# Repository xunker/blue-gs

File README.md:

# BlueGS: Internal BlueSCSI for Apple IIgs and //e

*BlueGS* is the internal hard drive your Apple IIgs and //e always *craved*.

Using the [BlueSCSI](https://github.com/erichelgeson/BlueSCSI) SCSI drive emulator and your compatible SCSI card, you have a fully internal hard drive with accessible microSD slot while still keeping your DB-25 connector free for other peripherals.

# How it works

BlueGS connects between your SCSI card and its external DB-25 connector to give you a seamless installation. The BlueGS module itself mounts in a free DB-25 connector cutout in the rear of your IIgs or //e.

# Features

* Gives your Apple IIgs or //e an internal, cable-free hard drive
* Can be powered from SCSI termination power only (if present)
* "Termination Power" mod is not required (when powered from auxiliary 5V source)
* Can *provide* termination power to the SCSI bus (when powered from a 5V source such as the Game IO connector or card slot)
* Built-in termination that is controlled with a single switch
* Active termination ICs instead of passive termination resistors, reduces power consumption by over 2/3rds
* Reverse current and voltage protection with overcurrent prevention for auxiliary 5V input
* Connection for external drive activity LED

# Compatible SCSI cards

Tested:
* [GGLabs A2SCSI](https://gglabs.us/node/2071) - a clone of the Apple Rev C SCSI card
* Apple Rev C SCSI and clones
* Apple High-Speed SCSI ("Sandwich II")
* Ramfast SCSI

Assumed to work:
* GSE-Reactive SCSI Card

Untested:
* AMR SCSI
* Cirtech SCSI/Insyder
* SVA Hard Disk Adapter

The CMS SCSI II is currently confirmed **NOT** to work, though it appears to be a (card) firmware issue and not a "bug" with BlueSCSI.

## What if my SCSI card doesn't provide termination power?

Running BlueGS from "termination power" makes installation much easier, but not all SCSI cards have it. For more details, please check out the notes on [Powering BlueGS](POWERING_BLUE-GS.md).

# Performance

Using [BenchmarkD](https://www.brutaldeluxe.fr/products/apple2gs/benchmarked.html) with Apple IIgs (ROM 1, "Fast" speed), GS-RAM Plus w/ 2MB, GGLabs A2SCSI card. Using Blue-Pill-based BlueGS board.

* Read
  * File: 52 KB/s
  * Block-by-block: 36 KB/s
  * With 64K buffer: 79 KB/s
* Write (File): 37 KB/s

# Can I use it on things besides the IIgs and //e?

Yes! It's a standard BlueSCSI device and uses the standard BlueSCSI V1 firmware. In fact, the built-in DB-25 connector makes it the perfect external SCSI drive as well!

BlueGS can be mounted internally in any computer that has an open cutout for a DB-25 connector.

## ✅ Compatible Apple clones

These computers *do* have rear DB-25 cutouts and so BlueGS should be able to mount properly, but are untested.

* Franklin Ace 2000/2100/2200
* Basis 108

## 🚫 Apple II/II+ and similar clones

BlueGS will function in an Apple II or II+, but you will not be able to mount it because it uses "V" shaped cutouts instead of D-Subminiature connector cutouts like the //e and IIgs have.

Many Apple II clones use the same rear cutout design and have the same mounting limitation. **A mounting solution for these machine is planned**.

* Franklin Ace 100/1000/1200
* Pravetz-8
  - Includes the -8, -82, -8M, -8A, -8E, and -8C
* Unitron (Brazil)
* Ci Base-48 and Pineapple (Korea)

# Assembly

If you purchased BlueGS as a self-assemble kit or are using your own PCBs, please follow the instructions in the "[assembly](assembly/)" directory.

If your BlueGS was purchased fully-assembled, please move on to the "[Installation](installation/)" section.
# Installation

Installation guides can be found in the "[installation](installation/)" directory.
# Schematics

[V1.4 Schematic](schematics/schematic_v1.4.pdf) (**FINAL**, recommended design)

<details>
  <summary>Older Schematics</summary>

[V1.3 Schematic](schematics/schematic_v1.3.pdf)

[V1.2 Schematic](schematics/schematic_v1.2.pdf)

[V1.1 Schematic](schematics/schematic_v1.1.pdf)

</details>

# EDA/Kicad and Gerber Files

Kicad of current design can be found in [kicad](kicad/) directory.

# Credits

This project would not be possible without the work done by [ztto](https://github.com/ztto/ArdSCSino-stm32), [Tambo](https://twitter.com/h_koma2), [Eric Helgeson](https://github.com/erichelgeson/BlueSCSI), [Androda](https://androda.work/), and many others.

The "Blue Pill" footprint was originally created by [Yet-Another-Average-Joe](https://github.com/yet-another-average-joe/Kicad-STM32).

Symbol and footprint for Molex 105162-0001 MicroSD slot created by [SnapEDA user HMantz](https://www.snapeda.com/parts/105162-0001/Molex/view-part/).

# License

See [LICENSE.md](LICENSE.md).

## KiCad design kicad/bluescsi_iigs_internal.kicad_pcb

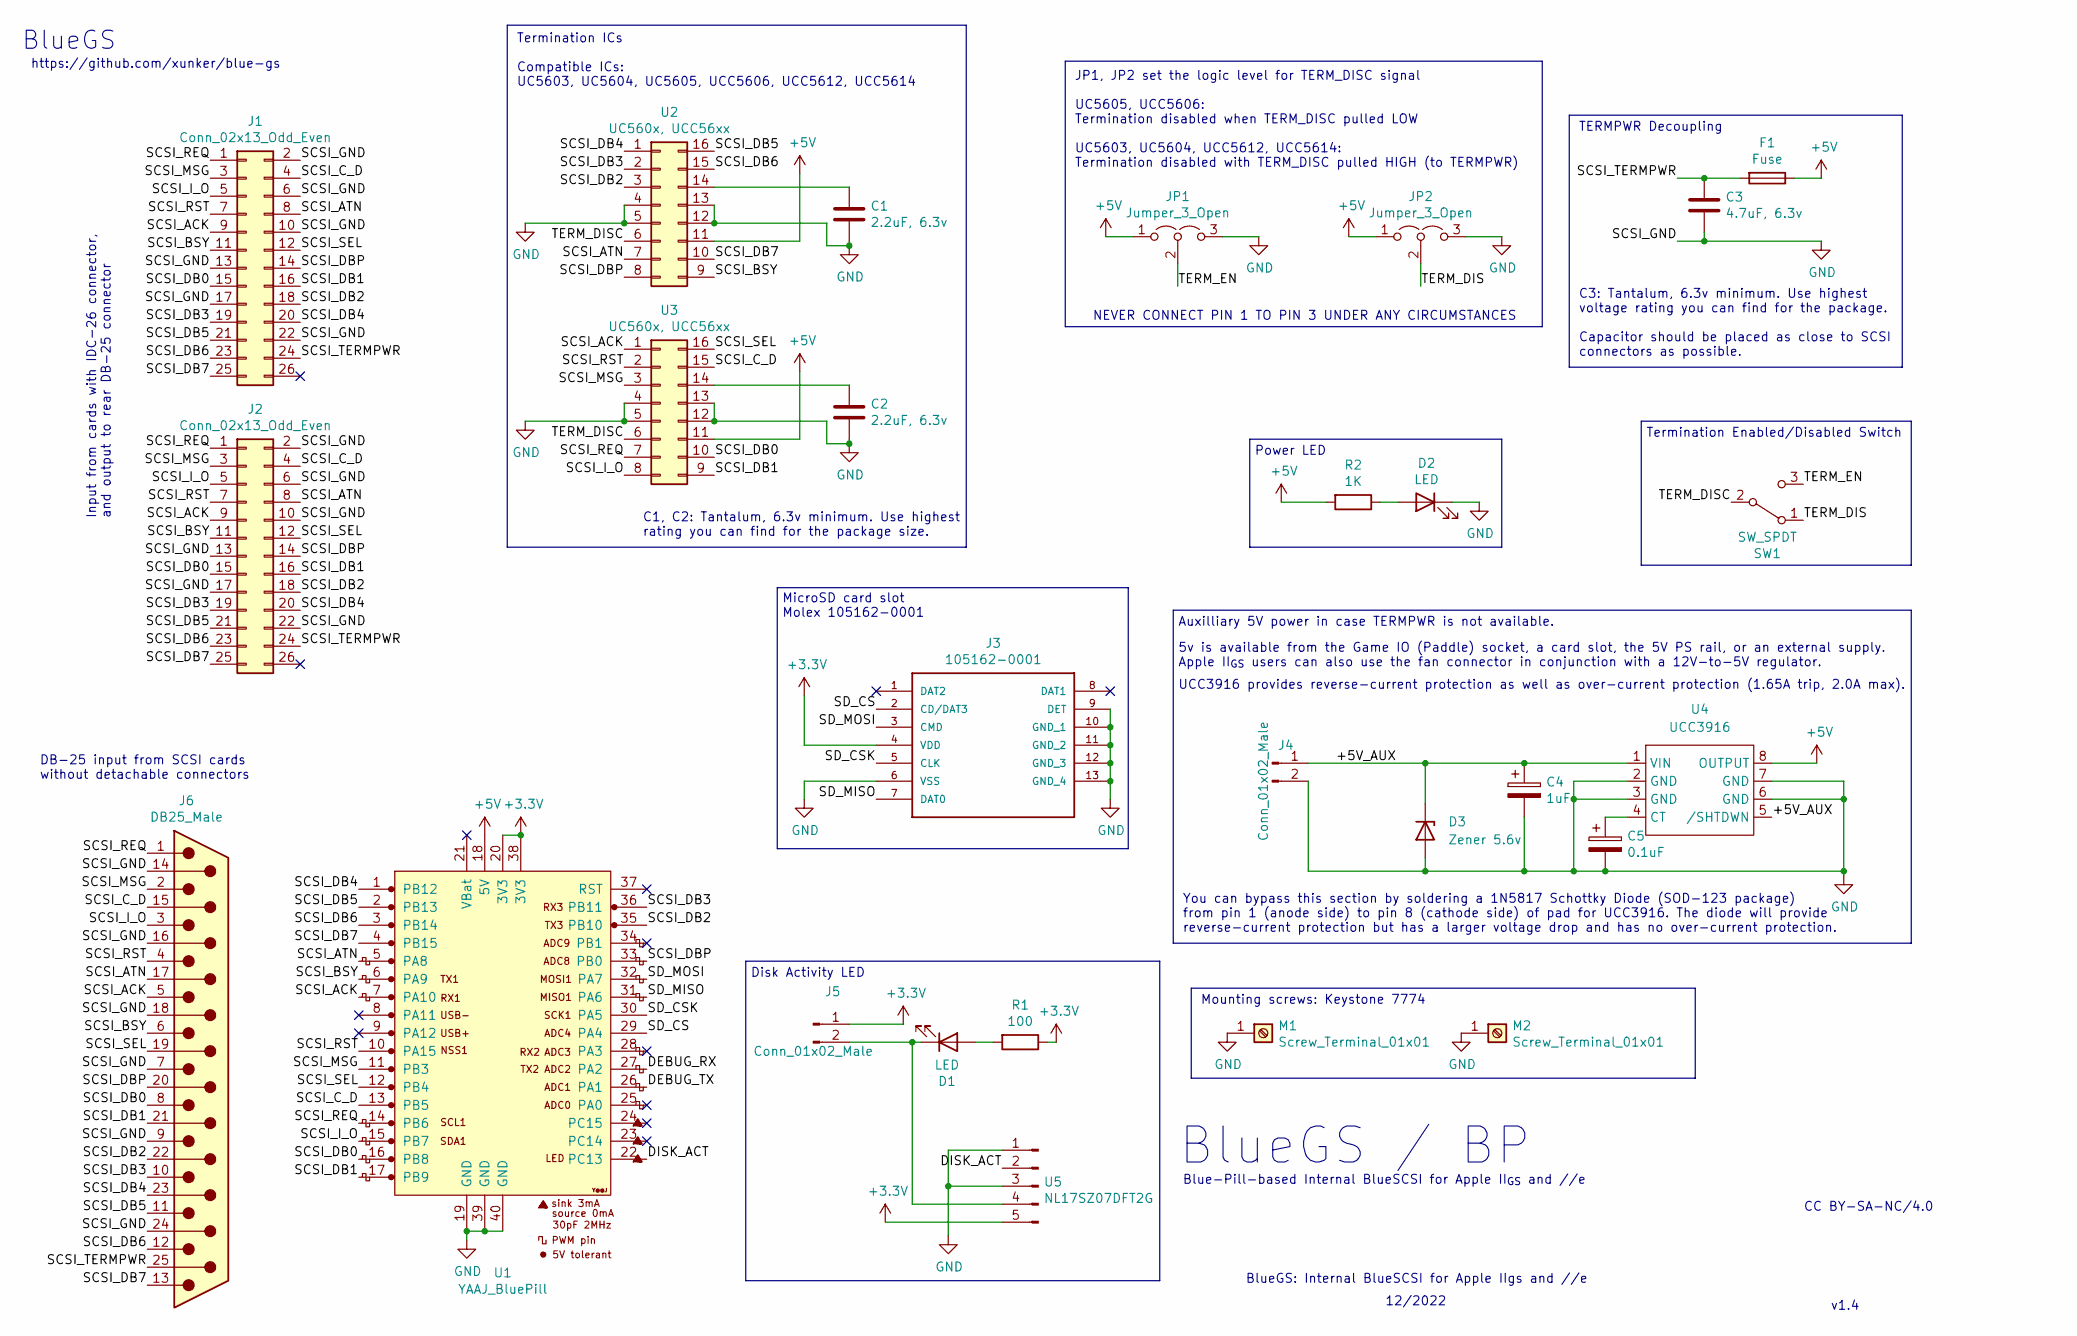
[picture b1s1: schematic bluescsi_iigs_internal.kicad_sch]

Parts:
C1, C2: 2.2uF, 6.3v; CP_EIA-3528-21_Kemet-B_Pad1.50x2.35mm_HandSolder; MANUFACTURER_PART_NUMBER TAJB225M020RNJ; LCSC part number C444753
C3: 4.7uF, 6.3v; CP_EIA-3528-21_Kemet-B_Pad1.50x2.35mm_HandSolder; MANUFACTURER_PART_NUMBER T494B475K016AT; LCSC part number C918865
C4: 1uF; CP_EIA-3528-21_Kemet-B_Pad1.50x2.35mm_HandSolder; MANUFACTURER_PART_NUMBER T491B105K025AT; LCSC part number C452761
C5: 0.1uF; CP_EIA-3216-10_Kemet-I; MANUFACTURER_PART_NUMBER T491A104K035AT; LCSC part number C122257
D1: LED; LED_0805_2012Metric_Pad1.15x1.40mm_HandSolder; MANUFACTURER_PART_NUMBER HL-PSC-2012H203BC; LCSC part number C497961
D2: LED; LED_0805_2012Metric_Pad1.15x1.40mm_HandSolder; MANUFACTURER_PART_NUMBER NCD0805R1; LCSC part number C84256
D3: Zener 5.6v; D_SOD-123; MANUFACTURER_PART_NUMBER MMSZ5232A_R1_00001; LCSC part number C268592
F1: Fuse; Fuse_1210_3225Metric; MANUFACTURER_PART_NUMBER CFS12V6TR80; LCSC part number C163134
J1, J2: Conn_02x13_Odd_Even; PinHeader_2x13_P2.54mm_Vertical
J3: 105162-0001; MOUSER_PART_NUMBER 538-105162-0001
J4, J5: Conn_01x02_Male; PinHeader_1x02_P2.54mm_Vertical
J6: DB25_Male; DSUB-25_Male_EdgeMount_P2.77mm
JP1, JP2: Jumper_3_Open; SolderJumper-3_P1.3mm_Open_Pad1.0x1.5mm_NumberLabels
M1, M2: Screw_Terminal_01x01; keystone-7774
R1: 100; R_0805_2012Metric_Pad1.20x1.40mm_HandSolder; MANUFACTURER_PART_NUMBER 0805W8F1000T5E; LCSC part number C17408
R2: 1K; R_0805_2012Metric_Pad1.20x1.40mm_HandSolder; MANUFACTURER_PART_NUMBER 0805W8F1001T5E; LCSC part number C17513
SW1: SW_SPDT; SW_SPDT_PCM12; MANUFACTURER_PART_NUMBER PCM12SMTR; LCSC part number C221841
U1: YAAJ_BluePill; YAAJ_BluePill_2
U2, U3: UC560x, UCC56xx; SOIC127P600X175-16N
U4: UCC3916; SOIC-8_3.9x4.9mm_P1.27mm
U5: NL17SZ07DFT2G; SOT-353_SC-70-5_Handsoldering; MANUFACTURER_PART_NUMBER NL17SZ07DFT2G; LCSC part number C113255

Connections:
+3V3: J3.4 (VDD), J5.1, R1.1, U1.20 (3V3), U1.38 (3V3), U5.5
+5V: F1.1, JP1.1 (A), JP2.1 (A), R2.2, U1.18 (5V), U2.11, U3.11, U4.8 (OUTPUT)
/+5V_AUX: C4.1, D3.1 (K), J4.1, U4.1 (VIN), U4.5 (/SHTDWN)
/DEBUG_RX: U1.27 (PA2)
/DEBUG_TX: U1.26 (PA1)
/DISK_ACT: U1.22 (PC13), U5.2
/SCSI_ACK: J1.9, J2.9, J6.5, U1.7 (PA10), U3.1
/SCSI_ATN: J1.8, J2.8, J6.17, U1.5 (PA8), U2.7
/SCSI_BSY: J1.11, J2.11, J6.6, U1.6 (PA9), U2.9
/SCSI_C_D: J1.4, J2.4, J6.15, U1.13 (PB5), U3.15
/SCSI_DB0: J1.15, J2.15, J6.8, U1.16 (PB8), U3.10
/SCSI_DB1: J1.16, J2.16, J6.21, U1.17 (PB9), U3.9
/SCSI_DB2: J1.18, J2.18, J6.22, U1.35 (PB10), U2.3
/SCSI_DB3: J1.19, J2.19, J6.10, U1.36 (PB11), U2.2
/SCSI_DB4: J1.20, J2.20, J6.23, U1.1 (PB12), U2.1
/SCSI_DB5: J1.21, J2.21, J6.11, U1.2 (PB13), U2.16
/SCSI_DB6: J1.23, J2.23, J6.12, U1.3 (PB14), U2.15
/SCSI_DB7: J1.25, J2.25, J6.13, U1.4 (PB15), U2.10
/SCSI_DBP: J1.14, J2.14, J6.20, U1.33 (PB0), U2.8
/SCSI_I_O: J1.5, J2.5, J6.3, U1.15 (PB7), U3.8
/SCSI_MSG: J1.3, J2.3, J6.2, U1.11 (PB3), U3.3
/SCSI_REQ: J1.1, J2.1, J6.1, U1.14 (PB6), U3.7
/SCSI_RST: J1.7, J2.7, J6.4, U1.10 (PA15), U3.2
/SCSI_SEL: J1.12, J2.12, J6.19, U1.12 (PB4), U3.16
/SCSI_TERMPWR: C3.1, F1.2, J1.24, J2.24, J6.25
/SD_CS: J3.2 (CD/DAT3), U1.29 (PA4)
/SD_CSK: J3.5 (CLK), U1.30 (PA5)
/SD_MISO: J3.7 (DAT0), U1.31 (PA6)
/SD_MOSI: J3.3 (CMD), U1.32 (PA7)
/TERM_DIS: JP2.2 (C), SW1.1 (A)
/TERM_DISC: SW1.2 (B), U2.6, U3.6
/TERM_EN: JP1.2 (C), SW1.3 (C)
GND: C1.2, C2.2, C3.2, C4.2, C5.2, D2.1 (K), D3.2 (A), J1.2, J1.6, J1.10, J1.13, J1.17, J1.22, J2.2, J2.6, J2.10, J2.13, J2.17, J2.22, J3.6 (VSS), J3.9 (DET), J3.10 (GND_1), J3.11 (GND_2), J3.12 (GND_3), J3.13 (GND_4), J4.2, J6.7, J6.9, J6.14, J6.16, J6.18, J6.24, JP1.3 (B), JP2.3 (B), M1.1, M2.1, U1.19 (GND), U1.39 (GND), U1.40 (GND), U2.4, U2.5, U2.12, U2.13, U3.4, U3.5, U3.12, U3.13, U4.2 (GND), U4.3 (GND), U4.6 (GND), U4.7 (GND), U5.1, U5.3
unnamed: C1.1, U2.14
unnamed: C2.1, U3.14
unnamed: C5.1, U4.4 (CT)
unnamed: D1.1 (K), J5.2, U5.4
unnamed: D1.2 (A), R1.2
unnamed: D2.2 (A), R2.1

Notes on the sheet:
C3: Tantalum, 6.3v minimum. Use highest voltage rating you can find for the package. Capacitor should be placed as close to SCSI connectors as possible.
BlueGS
NEVER CONNECT PIN 1 TO PIN 3 UNDER ANY CIRCUMSTANCES
Termination Enabled/Disabled Switch
5v is available from the Game IO (Paddle) socket, a card slot, the 5V PS rail, or an external supply. Apple II_{GS} users can also use the fan connector in conjunction with a 12V-to-5V regulator.
BlueGS / BP
12/2022
Power LED
https://github.com/xunker/blue-gs
CC BY-SA-NC/4.0
JP1, JP2 set the logic level for TERM_DISC signal UC5605, UCC5606: Termination disabled when TERM_DISC pulled LOW UC5603, UC5604, UCC5612, UCC5614: Termination disabled with TERM_DISC pulled HIGH (to TERMPWR)
DB-25 input from SCSI cards without detachable connectors
UCC3916 provides reverse-current protection as well as over-current protection (1.65A trip, 2.0A max).
C1, C2: Tantalum, 6.3v minimum. Use highest rating you can find for the package size.
You can bypass this section by soldering a 1N5817 Schottky Diode (SOD-123 package) from pin 1 (anode side) to pin 8 (cathode side) of pad for UCC3916. The diode will provide reverse-current protection but has a larger voltage drop and has no over-current protection.
Mounting screws: Keystone 7774
Auxilliary 5V power in case TERMPWR is not available.
Blue-Pill-based Internal BlueSCSI for Apple II_{GS} and //e
BlueGS: Internal BlueSCSI for Apple IIgs and //e
Disk Activity LED
Input from cards with IDC-26 connector, and output to rear DB-25 connector
MicroSD card slot Molex 105162-0001
TERMPWR Decoupling
Termination ICs Compatible ICs: UC5603, UC5604, UC5605, UCC5606, UCC5612, UCC5614
v1.4

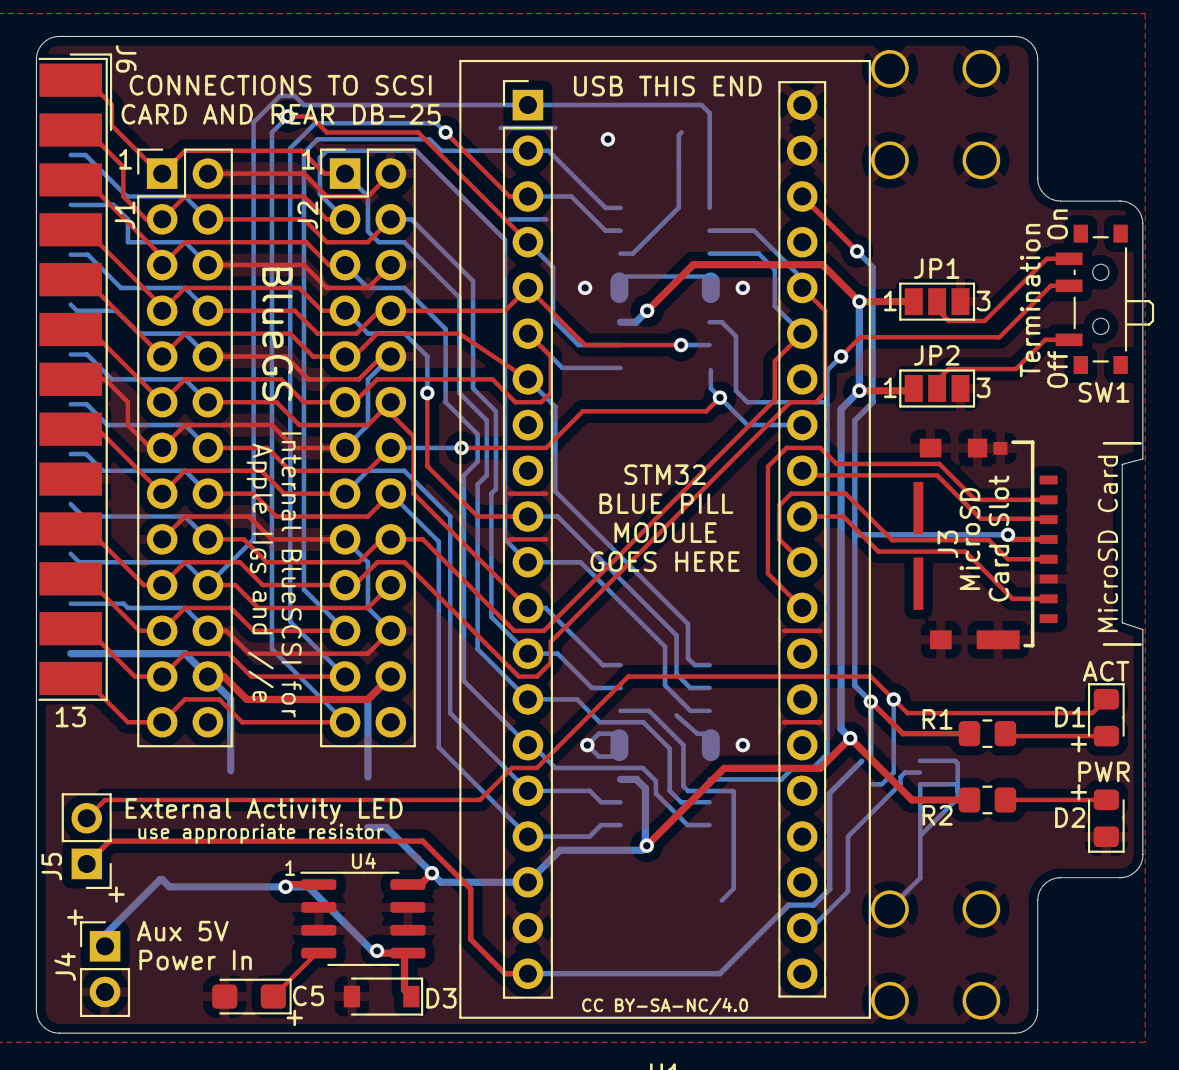
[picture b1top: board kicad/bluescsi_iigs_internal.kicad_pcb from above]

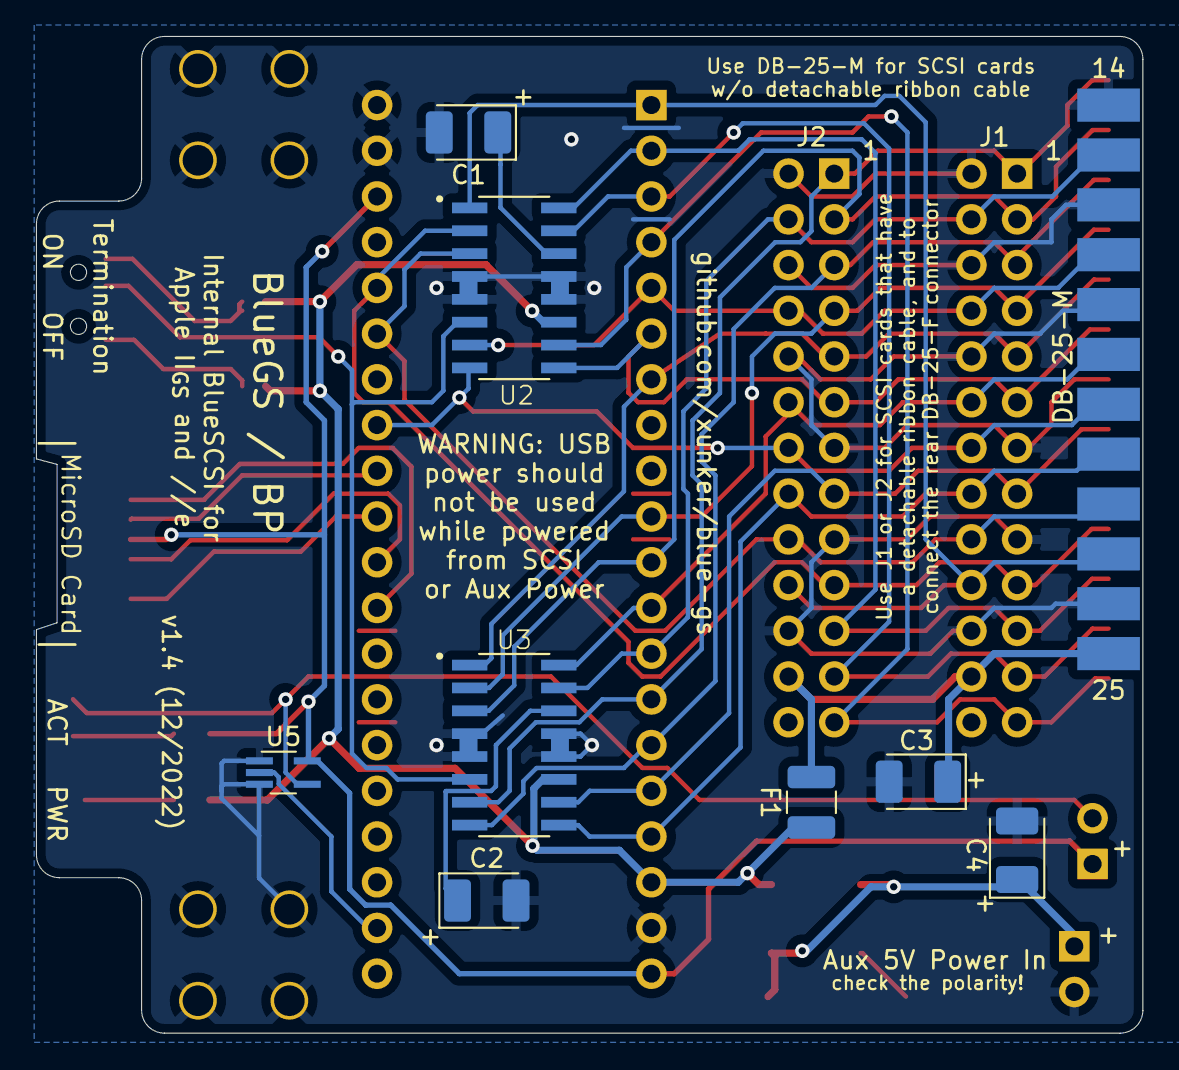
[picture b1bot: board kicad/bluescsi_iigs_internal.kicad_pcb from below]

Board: 2 copper layers, 61.5 x 55.4 mm, 27 parts (8 on the bottom side), 37 nets.

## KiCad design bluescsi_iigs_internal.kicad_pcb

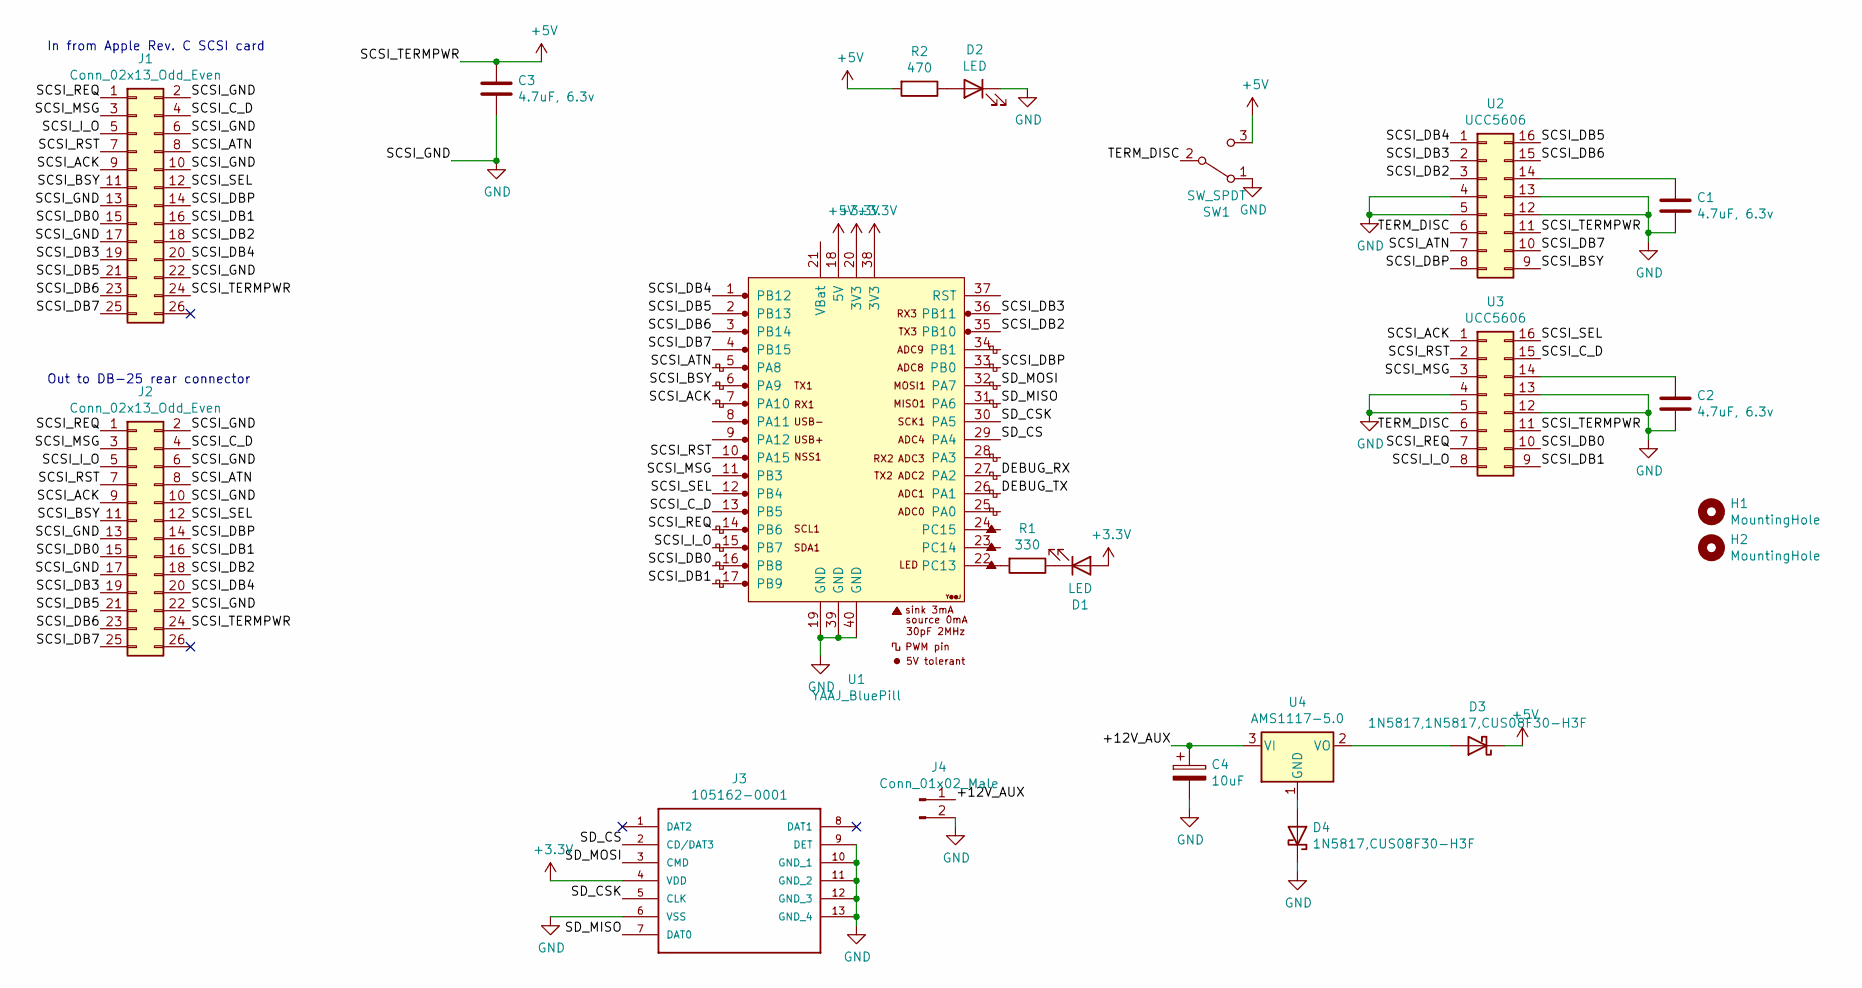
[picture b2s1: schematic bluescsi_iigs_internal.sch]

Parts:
C1, C2, C3: 4.7uF, 6.3v; CP_EIA-3528-21_Kemet-B_Pad1.50x2.35mm_HandSolder
C4: 10uF; CP_EIA-3528-21_Kemet-B_Pad1.50x2.35mm_HandSolder
D1, D2: LED; LED_0805_2012Metric_Pad1.15x1.40mm_HandSolder
D3: 1N5817,1N5817,CUS08F30-H3F; D_SOD-323_HandSoldering
D4: 1N5817,CUS08F30-H3F; D_SOD-323_HandSoldering
H1, H2: MountingHole; MountingHole_3mm
J1, J2: Conn_02x13_Odd_Even; PinHeader_2x13_P2.54mm_Vertical
J3: 105162-0001; MOUSER_PART_NUMBER 538-105162-0001
J4: Conn_01x02_Male; PinHeader_1x02_P2.54mm_Vertical
R1: 330; R_0805_2012Metric_Pad1.20x1.40mm_HandSolder
R2: 470; R_0805_2012Metric_Pad1.20x1.40mm_HandSolder
SW1: SW_SPDT; SW_SPDT_PCM12
U1: YAAJ_BluePill; YAAJ_BluePill_2
U2, U3: UCC5606; SOIC127P600X175-16N
U4: AMS1117-5.0; SOT-223-3_TabPin2

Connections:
+3V3: D1.2 (A), J3.4 (VDD), U1.20 (3V3), U1.38 (3V3)
+5V: C3.1, D3.1 (K), J1.24, J2.24, R2.2, SW1.3 (C), U1.18 (5V), U2.11, U3.11
/+12V_AUX: C4.1, J4.1, U4.3 (VI)
/DEBUG_RX: U1.27 (PA2)
/DEBUG_TX: U1.26 (PA1)
/SCSI_ACK: J1.9, J2.9, U1.7 (PA10), U3.1
/SCSI_ATN: J1.8, J2.8, U1.5 (PA8), U2.7
/SCSI_BSY: J1.11, J2.11, U1.6 (PA9), U2.9
/SCSI_C_D: J1.4, J2.4, U1.13 (PB5), U3.15
/SCSI_DB0: J1.15, J2.15, U1.16 (PB8), U3.10
/SCSI_DB1: J1.16, J2.16, U1.17 (PB9), U3.9
/SCSI_DB2: J1.18, J2.18, U1.35 (PB10), U2.3
/SCSI_DB3: J1.19, J2.19, U1.36 (PB11), U2.2
/SCSI_DB4: J1.20, J2.20, U1.1 (PB12), U2.1
/SCSI_DB5: J1.21, J2.21, U1.2 (PB13), U2.16
/SCSI_DB6: J1.23, J2.23, U1.3 (PB14), U2.15
/SCSI_DB7: J1.25, J2.25, U1.4 (PB15), U2.10
/SCSI_DBP: J1.14, J2.14, U1.33 (PB0), U2.8
/SCSI_I_O: J1.5, J2.5, U1.15 (PB7), U3.8
/SCSI_MSG: J1.3, J2.3, U1.11 (PB3), U3.3
/SCSI_REQ: J1.1, J2.1, U1.14 (PB6), U3.7
/SCSI_RST: J1.7, J2.7, U1.10 (PA15), U3.2
/SCSI_SEL: J1.12, J2.12, U1.12 (PB4), U3.16
/SD_CS: J3.2 (CD/DAT3), U1.29 (PA4)
/SD_CSK: J3.5 (CLK), U1.30 (PA5)
/SD_MISO: J3.7 (DAT0), U1.31 (PA6)
/SD_MOSI: J3.3 (CMD), U1.32 (PA7)
/TERM_DISC: SW1.2 (B), U2.6, U3.6
GND: C1.2, C2.2, C3.2, C4.2, D2.1 (K), D4.1 (K), J1.2, J1.6, J1.10, J1.13, J1.17, J1.22, J2.2, J2.6, J2.10, J2.13, J2.17, J2.22, J3.6 (VSS), J3.9 (DET), J3.10 (GND_1), J3.11 (GND_2), J3.12 (GND_3), J3.13 (GND_4), J4.2, SW1.1 (A), U1.19 (GND), U1.39 (GND), U1.40 (GND), U2.4, U2.5, U2.12, U2.13, U3.4, U3.5, U3.12, U3.13
unnamed: C1.1, U2.14
unnamed: C2.1, U3.14
unnamed: D1.1 (K), R1.1
unnamed: D2.2 (A), R2.1
unnamed: D3.2 (A), U4.2 (VO)
unnamed: D4.2 (A), U4.1 (GND)
unnamed: R1.2, U1.22 (PC13)

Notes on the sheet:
In from Apple Rev. C SCSI card
Out to DB-25 rear connector

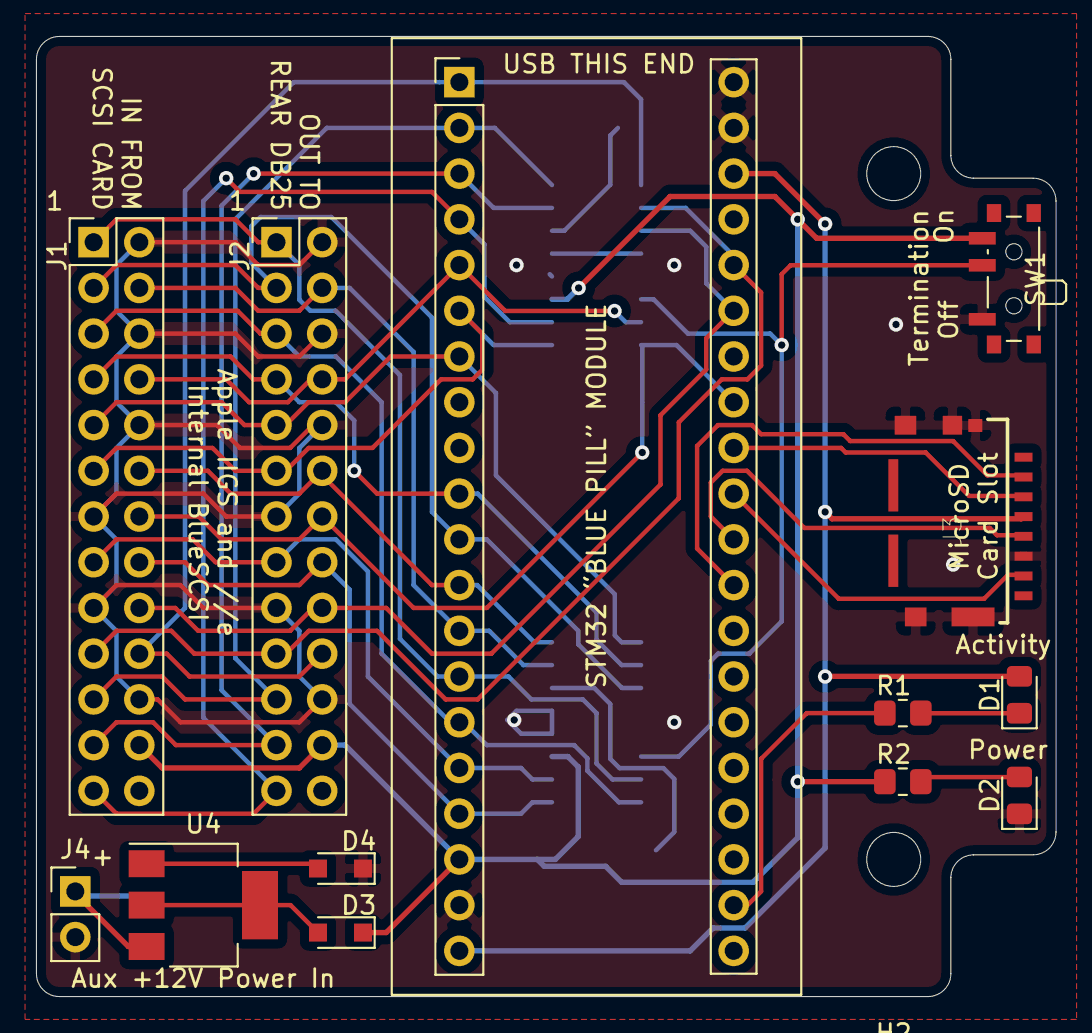
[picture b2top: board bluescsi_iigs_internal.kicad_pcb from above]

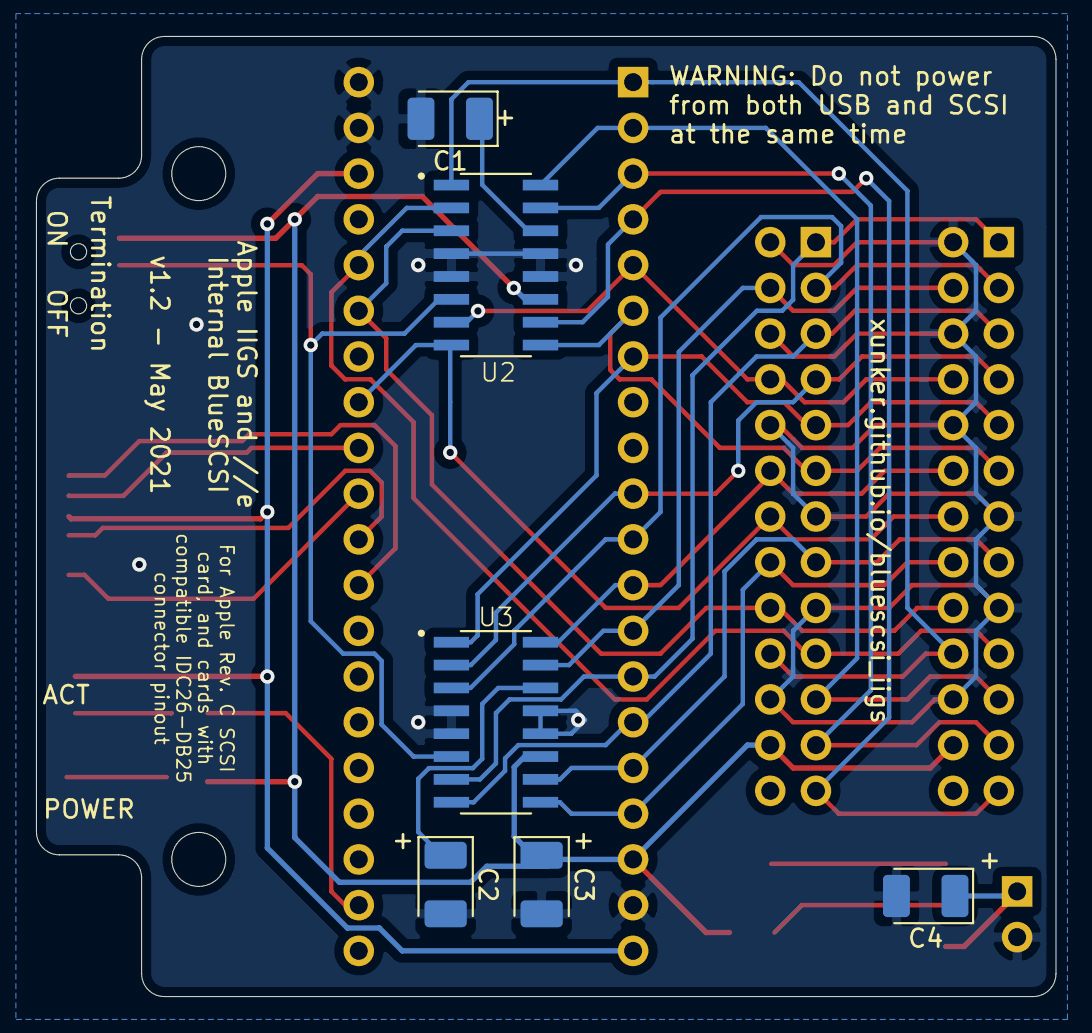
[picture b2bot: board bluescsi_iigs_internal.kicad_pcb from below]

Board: 2 copper layers, 56.6 x 53.3 mm, 21 parts (6 on the bottom side), 34 nets.

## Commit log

2021-04-02 Initial commit after v1.0 to fab
2021-04-12 V1.1 from v1.0 Fix IDC26 pin header to be correct! Change capacitor footprint to handsolder variant. Move mounting holes toward centre by about 2.54 and back by 2.54
2021-04-12 Increase trace size for +3.3v and +5v
2021-04-23 Fix db25 connector wiring
2021-04-23 move "shoulders" back more
2021-04-23 fix spacing
2021-04-23 Move mounting hole toward centre a bunch
2021-04-23 moving traces around
2021-04-25 Initial commit of pictures of v0 after bodging fix
2021-04-25 change radius of inside shoulder to match outside
2021-04-25 Change switch to smd
2021-04-25 pull back the shoulders even more
2021-04-25 nudge leds, add groind vias
2021-04-25 nudge the switch out a little, since ground can still pass underneath it
2021-04-26 Add auxilliary 12v input
2021-04-26 Change footprint of diodes
2021-04-28 Change microsd slot to Molex 105162-0001. Add version number to back silkscreen
2021-04-28 Remove UCC5606 from rear silk since will make this compatible with other ICs in future
2021-04-28 move rear termination text away from switch holes
2021-04-28 Add JPs to set the DISCNT signal level for compatibility with UC560x, UCC560x and UCC5612 terminator ICs
2021-04-30 Move kicad files to own directory
2021-04-30 remove the moved files
2021-05-01 Added an ignore file, isn't that ironic?
2021-05-01 Updated schematic to group items and make them more readable
2021-05-01 Add License
2021-05-01 Added rendered images and schematic of v1.2
2021-05-01 Added schematic of v1.1
2021-05-01 Shell for README
2021-05-01 Update silkscreens: * Power Warning * Nameing * URL
2021-05-01 Move via so both ground planes connect
2021-05-04 Name change to "Blue-GS"
2021-05-04 Add notes about termination ics
2021-05-04 Update notes about which JP setting to use with UCC5612
2021-05-10 Add fuse
2021-05-10 Increate termpwr track size
2021-05-10 Add another grounding track
2021-05-10 Add footprint for keystone 7774
2021-05-13 Added Fuse and LED driver mosfet
2021-05-13 Add p-mosfet driver for activity LED
2021-05-13 Added connector for external activity LED
2021-05-14 Replace mounting holes with Keystone 7774 brackets
2021-05-17 Adjust screw hole in slightly to account for screw width add silkscreen on rear for card slot
2021-05-17 Rear view a slightly different angle to force git commit
2021-05-17 fix front view file
2021-05-17 Added led credit to readme
2021-06-03 pth regulator hanging off the side
2021-06-03 move d3 a bit
2021-06-03 replace lef mostfest with logic inverter
2021-06-03 Change regulator to back side tab up
2021-06-03 enlarge power tracks slightly
2021-06-03 snug disk_act line in slightly
2021-06-03 pushing traces around to maximize ground fill
2021-06-10 Correct LED wiring for active-low with buffer IC
2021-06-10 Move the CD card slot back by about 3mm to protect the card more
2021-06-15 Added rear slot cover for v1.2
2021-06-15 Add v1.2 installed images
2021-06-15 Update readme to include pictures of v1.2 installed, and more details of installation
2021-06-15 Added basic installation guide
2021-06-15 Fix assembly ToC
2021-06-15 Remove URLs from sub-pages
2021-06-15 Added installtion images
2021-06-17 Added annotated pictures of v1.2 board
2021-06-17 Added v1.2 gerbers
2021-06-17 Added schematic for v1.3 (non-final), removed rendered board pictures not that we have REAL pictureds
2021-06-18 Added file detailing the ways to power BlueGS and which scsi cards have term power
2021-06-21 Add edge-mount db-25-m for scsi cards with fixed cables
2021-06-21 Move db-25-m further up to help cable routing
2021-06-21 Move microsd silkscreen to match new placment, add marker on front for same
2021-06-21 move the regulator around so the screw hole doesn't overlap the blue pill footprint
2021-06-21 Change silkscreens and legends, reroute 3.3v line for better grounding
2021-06-21 move some vias for better ground fill
2021-06-21 Re-annotate schematic for connectors add SN field
2022-10-07 v1.3.1 commit
2022-11-20 I should have done a changelog a long time ago
2022-11-20 retroactively add v1.3.1 gerbers
2022-11-20 Add new v1.4 gerbers
2022-11-20 created new symbol for UCC3916
2022-11-20 Change 7805 to UCC3916; nudge some traces to get better gnds
2022-12-02 Move power and led headers to better positon; Add indentation around microsd slot
2022-12-02 added part numbers
2022-12-02 Increase card indent, change C5 footprint
2022-12-02 Added compatibility for 74LVC1G125SE in place of NL17SZ07DFT2G
2022-12-02 Push traces around, remove a hyphen
2022-12-05 not necessary to commit
2022-12-05 Ignore fp-info-cache
2022-12-05 Make name more consistent, move sinkscreens around to make things look better
2022-12-05 Move power controller to front for better wire clearance in tight cases
2022-12-05 Move Termpower decoupling cap closer to the connector (as per specs)
2022-12-05 ignore autosave files
2022-12-05 straighter shot for DBP line
2022-12-05 Push more traces around to maximize infill
2022-12-05 Move some capacitors around, add more silkscreen notes
2022-12-05 shove trace away from via a little
2022-12-05 Push C4 a little higher to get it out of the way pf wires
2022-12-05 Give that via more space, we have it!
2022-12-05 move 3v3 via slightly so its inline with others
2022-12-05 Add silkscreen notes about connections
2022-12-13 Oshpark test fab
2022-12-16 move aux 5v connector a bit lower
2022-12-19 move silks around
2022-12-19 Fix overlapping text; change CC back to silkscreen
2023-01-26 schematics for working 1.4
2023-01-26 Change board branding to "BlueGS / BP" to distinguish it from rp2040-based design. Move cd card slot back slightly.
2023-01-26 remove TOC
2023-01-26 Update docs to refect removal of 12V Aux, and for branding changes
2023-01-26 Additional card compatibility notes
2023-01-26 Remove URL at top of readme because, like, you're already here, man.
2023-01-26 added notes about clone compatibility
2023-01-26 typo fix
